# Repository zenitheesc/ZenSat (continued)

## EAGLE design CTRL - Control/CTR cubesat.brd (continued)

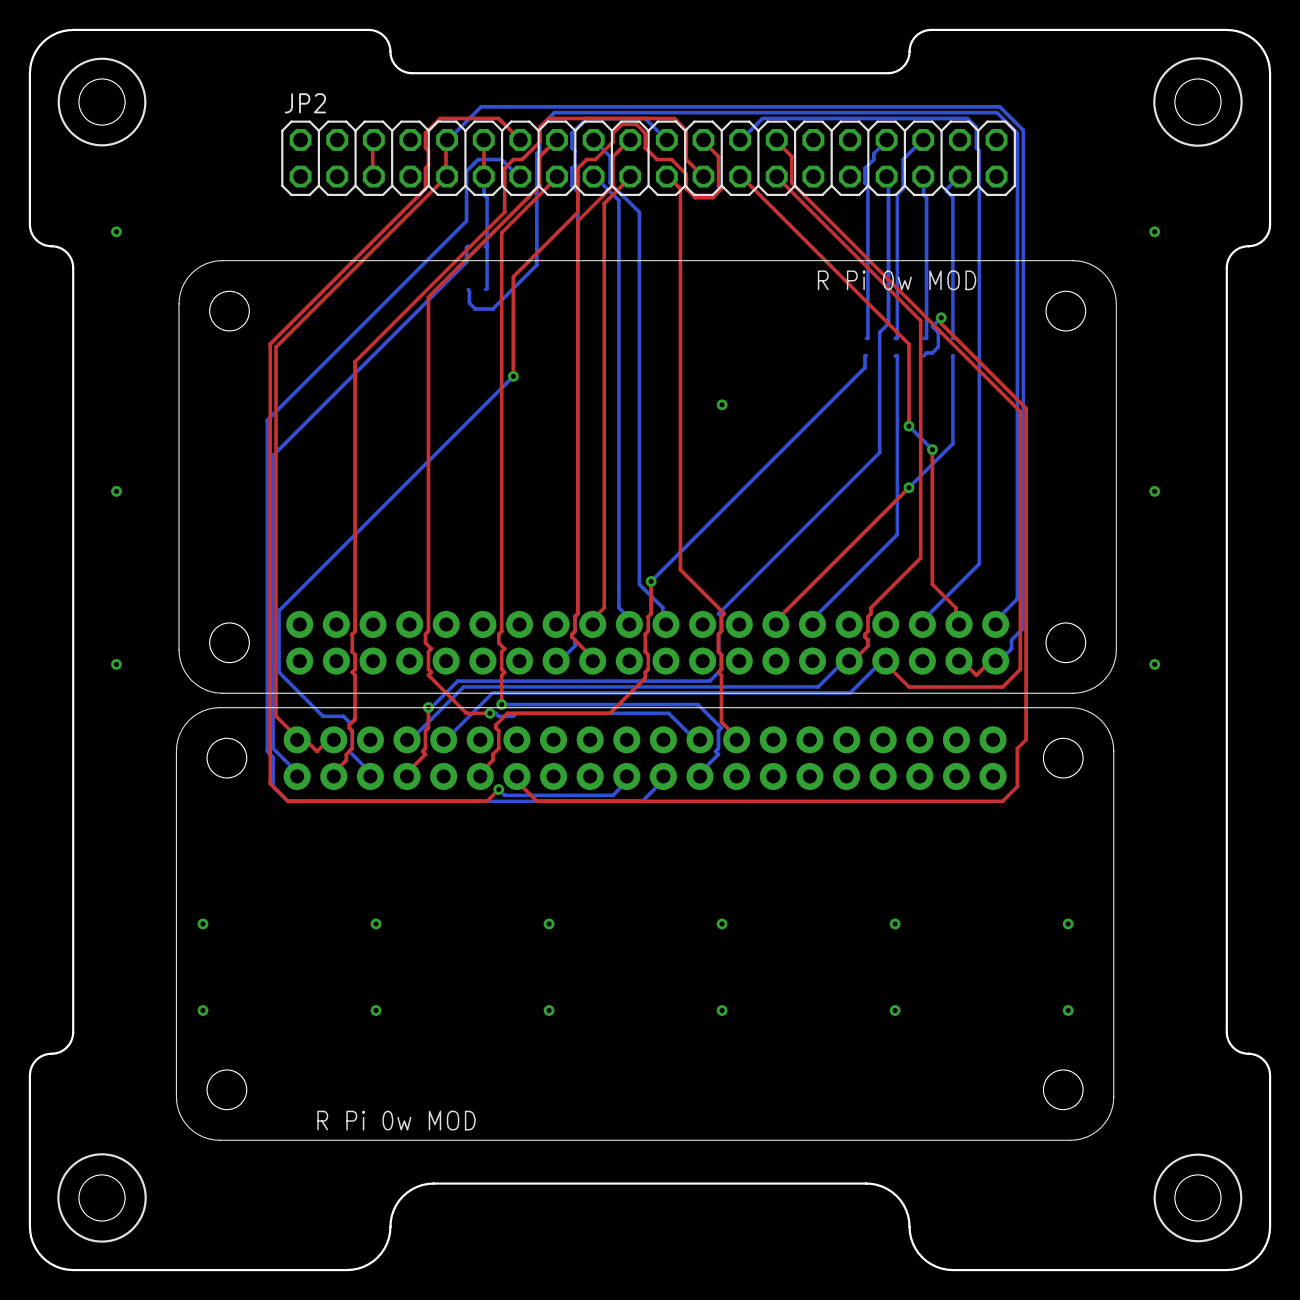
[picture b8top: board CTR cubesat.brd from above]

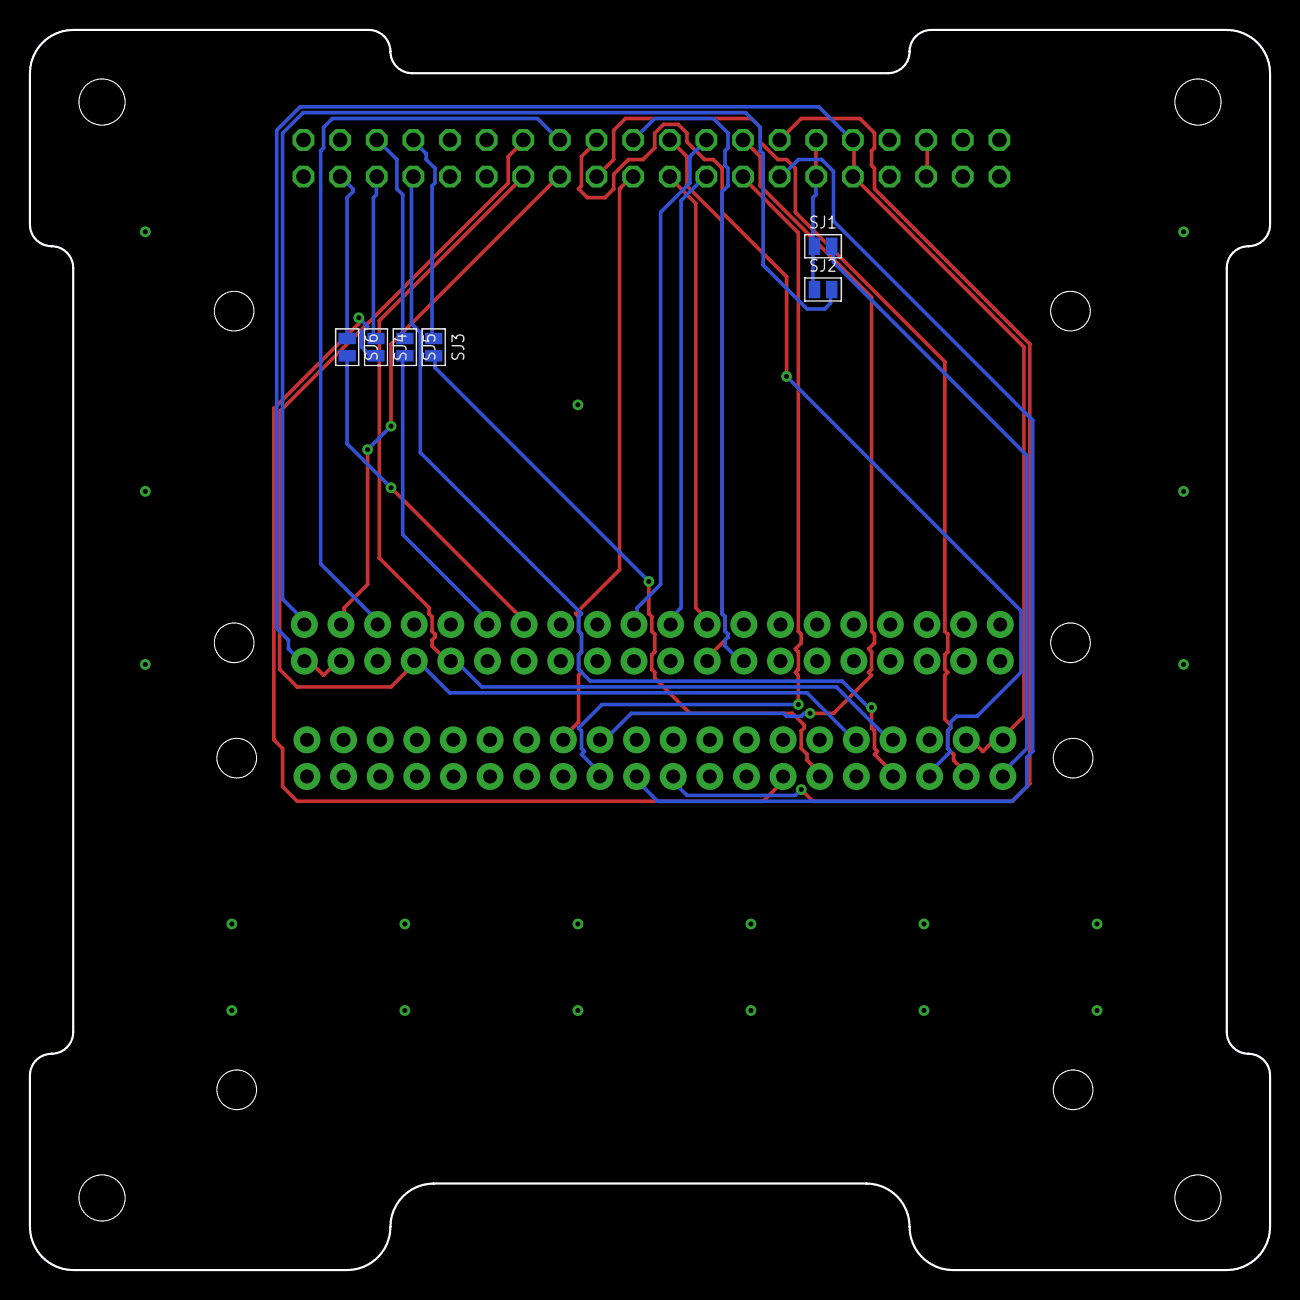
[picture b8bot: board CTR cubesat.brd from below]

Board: 2 copper layers, 86.0 x 86.0 mm, 9 parts (6 on the bottom side), 31 nets.

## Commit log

2018-07-13 RW_Test_1
    Controls the BLDC motor with the DRV Texas Driver by PWM
2018-07-13 ADC_Test_1
    PWM for DRV Texas Driver
2018-07-13 915MHz_LoRa_Sender
    Template for the ZenSat 1.0 TM system
2018-07-13 915MHz_LoRa_Receiver
    Template for the ZenSat 1.0 TM system
2018-07-13 Encoder_1.0
    IR based encoder ZenSat system
2018-07-15 Teste ina219 - Python - Barramento I2C 1 (Master)
2018-07-16 Update ADC_Test_1
    Implementado - encoder
2018-07-16 Update Encoder_1.0
    Implementado com. i2c
2018-07-17 Create ADC_STM32_master
    Rasp - atmega via SPI
    Atmega - STM via I2C
2018-07-17 Rename ADC_STM32_master to ADC_STM32_master.ino
2018-07-19 Add. "stabilize to an angle" function
    Not tested with the AC system
2018-07-25 Update adc_mvp.ino
    Send R to run
2021-03-29 Documentation
2021-03-29 images
2021-03-29 Cortes nas imgs
2021-04-20 adding CTRL software files
2021-04-20 adding block diagram image
